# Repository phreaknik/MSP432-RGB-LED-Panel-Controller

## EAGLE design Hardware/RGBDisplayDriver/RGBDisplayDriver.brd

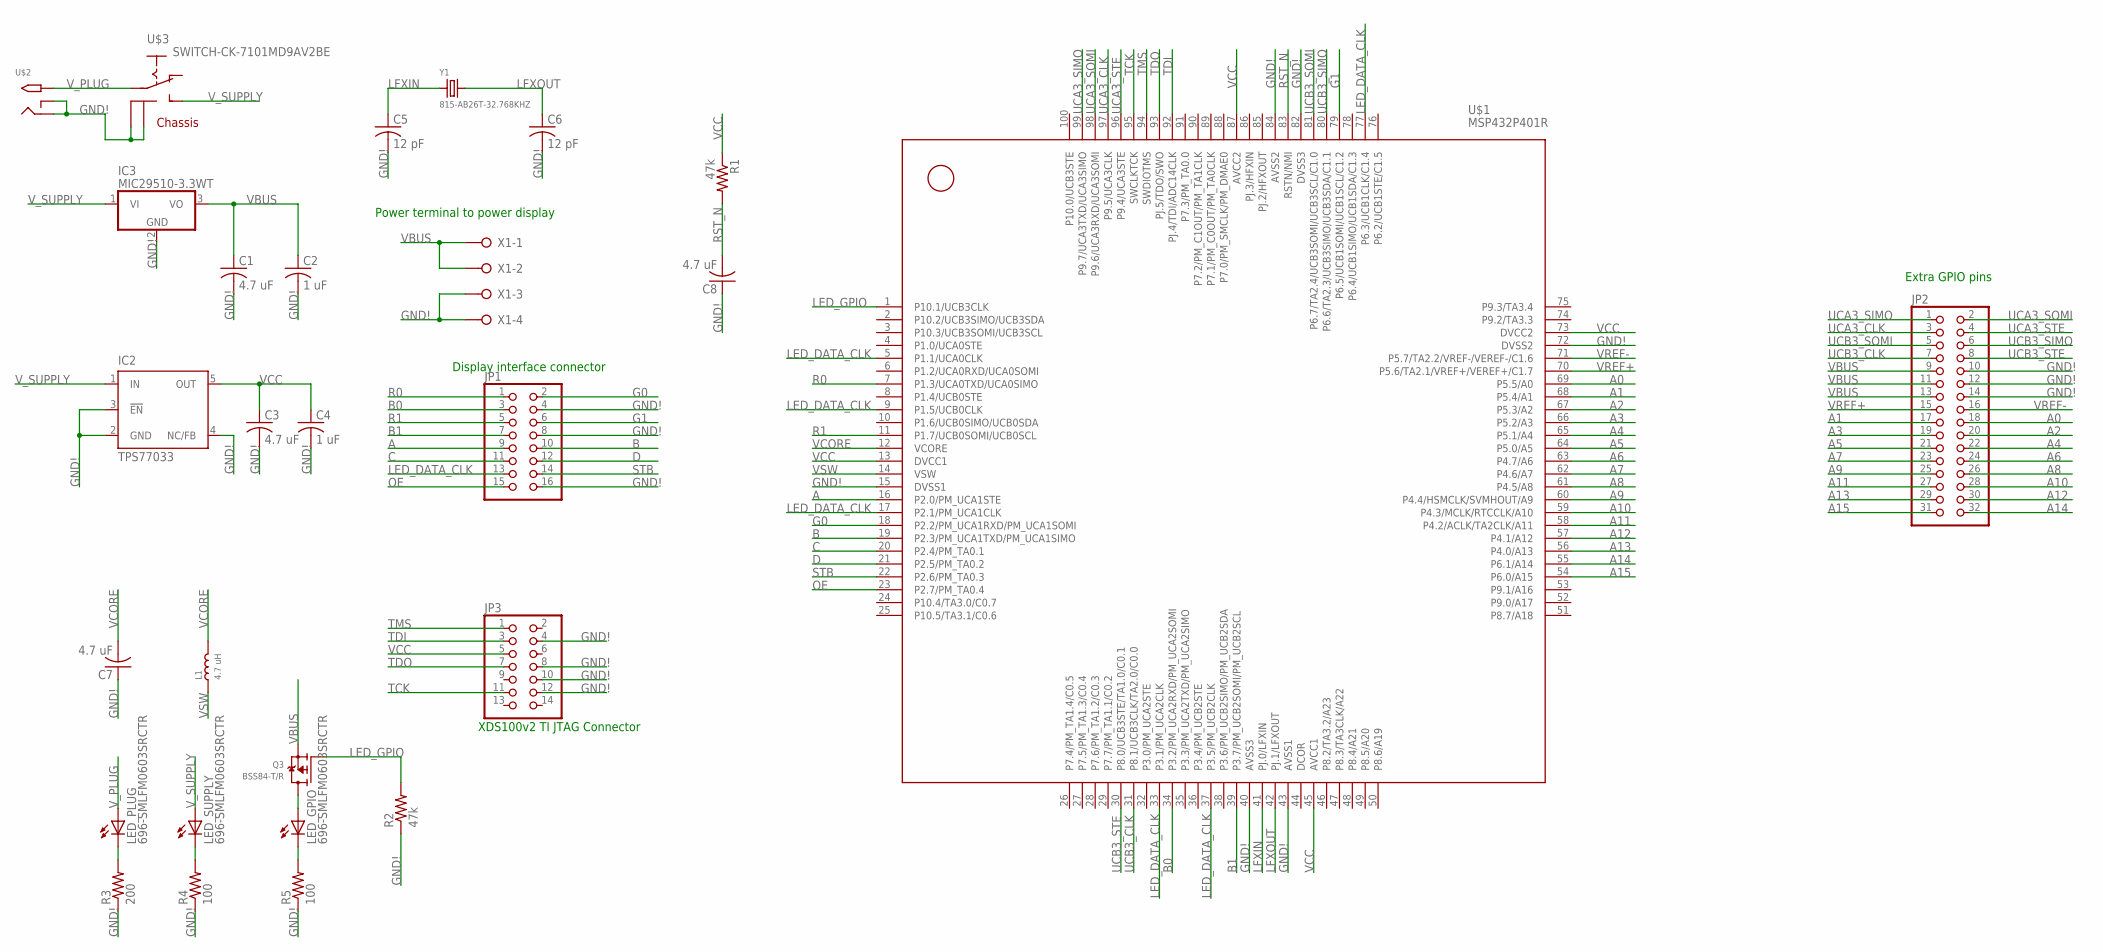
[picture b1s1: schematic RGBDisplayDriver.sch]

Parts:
C1, C3, C7, C8: 4.7 uF; C0603
C2, C4: 1 uF; C0603
C5, C6: 12 pF; C0603
IC2: TPS77033; SOT23-DBV
IC3: MIC29510-3.3WT; TO220V
JP1: PINHD-2X8; 2X08
JP2: PINHD-2X16; 2X16
JP3: PINHD-2X7; 2X07
L1: 4.7 uH; L0603
LED_GPIO: 696-SMLFM0603SRCTR; CHIPLED_0603
LED_PLUG: 696-SMLFM0603SRCTR; CHIPLED_0603
LED_SUPPLY: 696-SMLFM0603SRCTR; CHIPLED_0603
Q3: BSS84-T/R; SOT23-WIDE
R1, R2: 47k; R0603
R3: 200; R0603
R4, R5: 100; R0603
U$1: MSP432P401R; LQFP100
U$2: 2.1MMJACKTHM; PJ-102A
U$3: SWITCH-CK-7101MD9AV2BE
X1: W237-04P; W237-4P
Y1: 815-AB26T-32.768KHZ; CRYSTAL_CYL_2X6MM_SMT

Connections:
A: JP1.9, U$1.16 (P2.0/PM_UCA1STE)
A0: JP2.18, U$1.69 (P5.5/A0)
A1: JP2.17, U$1.68 (P5.4/A1)
A2: JP2.20, U$1.67 (P5.3/A2)
A3: JP2.19, U$1.66 (P5.2/A3)
A4: JP2.22, U$1.65 (P5.1/A4)
A5: JP2.21, U$1.64 (P5.0/A5)
A6: JP2.24, U$1.63 (P4.7/A6)
A7: JP2.23, U$1.62 (P4.6/A7)
A8: JP2.26, U$1.61 (P4.5/A8)
A9: JP2.25, U$1.60 (P4.4/HSMCLK/SVMHOUT/A9)
A10: JP2.28, U$1.59 (P4.3/MCLK/RTCCLK/A10)
A11: JP2.27, U$1.58 (P4.2/ACLK/TA2CLK/A11)
A12: JP2.30, U$1.57 (P4.1/A12)
A13: JP2.29, U$1.56 (P4.0/A13)
A14: JP2.32, U$1.55 (P6.1/A14)
A15: JP2.31, U$1.54 (P6.0/A15)
B: JP1.10, U$1.19 (P2.3/PM_UCA1TXD/PM_UCA1SIMO)
B0: JP1.3, U$1.34 (P3.2/PM_UCA2RXD/PM_UCA2SOMI)
B1: JP1.7, U$1.39 (P3.7/PM_UCB2SOMI/PM_UCB2SCL)
C: JP1.11, U$1.20 (P2.4/PM_TA0.1)
D: JP1.12, U$1.21 (P2.5/PM_TA0.2)
G0: JP1.2, U$1.18 (P2.2/PM_UCA1RXD/PM_UCA1SOMI)
G1: JP1.6, U$1.79 (P6.5/UCB1SOMI/UCB1SCL/C1.2)
GND!: C1.2, C2.2, C3.2, C4.2, C5.2, C6.2, C7.1, C8.1, IC2.2 (GND), IC2.3 (!EN), IC2.4 (NC/FB), IC3.2 (GND), JP1.4, JP1.8, JP1.16, JP2.10, JP2.12, JP2.14, JP3.4, JP3.8, JP3.10, JP3.12, R2.1, R3.1, R4.1, R5.1, U$1.15 (DVSS1), U$1.40 (AVSS3), U$1.43 (AVSS1), U$1.72 (DVSS2), U$1.82 (DVSS3), U$1.84 (AVSS2), U$2.RING, U$2.RING_SW, U$3.P$4, U$3.P$5, X1.3, X1.4
LED_DATA_CLK: JP1.13, U$1.5 (P1.1/UCA0CLK), U$1.9 (P1.5/UCB0CLK), U$1.17 (P2.1/PM_UCA1CLK), U$1.33 (P3.1/PM_UCA2CLK), U$1.37 (P3.5/PM_UCB2CLK), U$1.77 (P6.3/UCB1CLK/C1.4)
LED_GPIO: Q3.1 (G), R2.2, U$1.1 (P10.1/UCB3CLK)
LFXIN: C5.1, U$1.41 (PJ.0/LFXIN), Y1.1
LFXOUT: C6.1, U$1.42 (PJ.1/LFXOUT), Y1.2
unnamed: LED_GPIO.A, Q3.3 (D)
unnamed: LED_PLUG.C, R3.2
unnamed: LED_SUPPLY.C, R4.2
unnamed: LED_GPIO.C, R5.2
OE: JP1.15, U$1.23 (P2.7/PM_TA0.4)
R0: JP1.1, U$1.7 (P1.3/UCA0TXD/UCA0SIMO)
R1: JP1.5, U$1.11 (P1.7/UCB0SOMI/UCB0SCL)
RST_N: C8.2, R1.2, U$1.83 (RSTN/NMI)
STB: JP1.14, U$1.22 (P2.6/PM_TA0.3)
TCK: JP3.11, U$1.95 (SWCLKTCK)
TDI: JP3.3, U$1.92 (PJ.4/TDI/ADC14CLK)
TDO: JP3.7, U$1.93 (PJ.5/TDO/SWO)
TMS: JP3.1, U$1.94 (SWDIOTMS)
UCA3_CLK: JP2.3, U$1.97 (P9.5/UCA3CLK)
UCA3_SIMO: JP2.1, U$1.99 (P9.7/UCA3TXD/UCA3SIMO)
UCA3_SOMI: JP2.2, U$1.98 (P9.6/UCA3RXD/UCA3SOMI)
UCA3_STE: JP2.4, U$1.96 (P9.4/UCA3STE)
UCB3_CLK: JP2.7, U$1.31 (P8.1/UCB3CLK/TA2.0/C0.0)
UCB3_SIMO: JP2.6, U$1.80 (P6.6/TA2.3/UCB3SIMO/UCB3SDA/C1.1)
UCB3_SOMI: JP2.5, U$1.81 (P6.7/TA2.4/UCB3SOMI/UCB3SCL/C1.0)
UCB3_STE: JP2.8, U$1.30 (P8.0/UCB3STE/TA1.0/C0.1)
VBUS: C1.1, C2.1, IC3.3 (VO), JP2.9, JP2.11, JP2.13, Q3.2 (S), X1.1, X1.2
VCC: C3.1, C4.1, IC2.5 (OUT), JP3.5, R1.1, U$1.13 (DVCC1), U$1.45 (AVCC1), U$1.73 (DVCC2), U$1.87 (AVCC2)
VCORE: C7.2, L1.2, U$1.12 (VCORE)
VREF+: JP2.15, U$1.70 (P5.6/TA2.1/VREF+/VEREF+/C1.7)
VREF-: JP2.16, U$1.71 (P5.7/TA2.2/VREF-/VEREF-/C1.6)
VSW: L1.1, U$1.14 (VSW)
V_PLUG: LED_PLUG.A, U$2.TIP, U$3.P$2
V_SUPPLY: IC2.1 (IN), IC3.1 (VI), LED_SUPPLY.A, U$3.P$1

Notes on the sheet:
Power terminal to power display
Display interface connector
Extra GPIO pins
XDS100v2 TI JTAG Connector

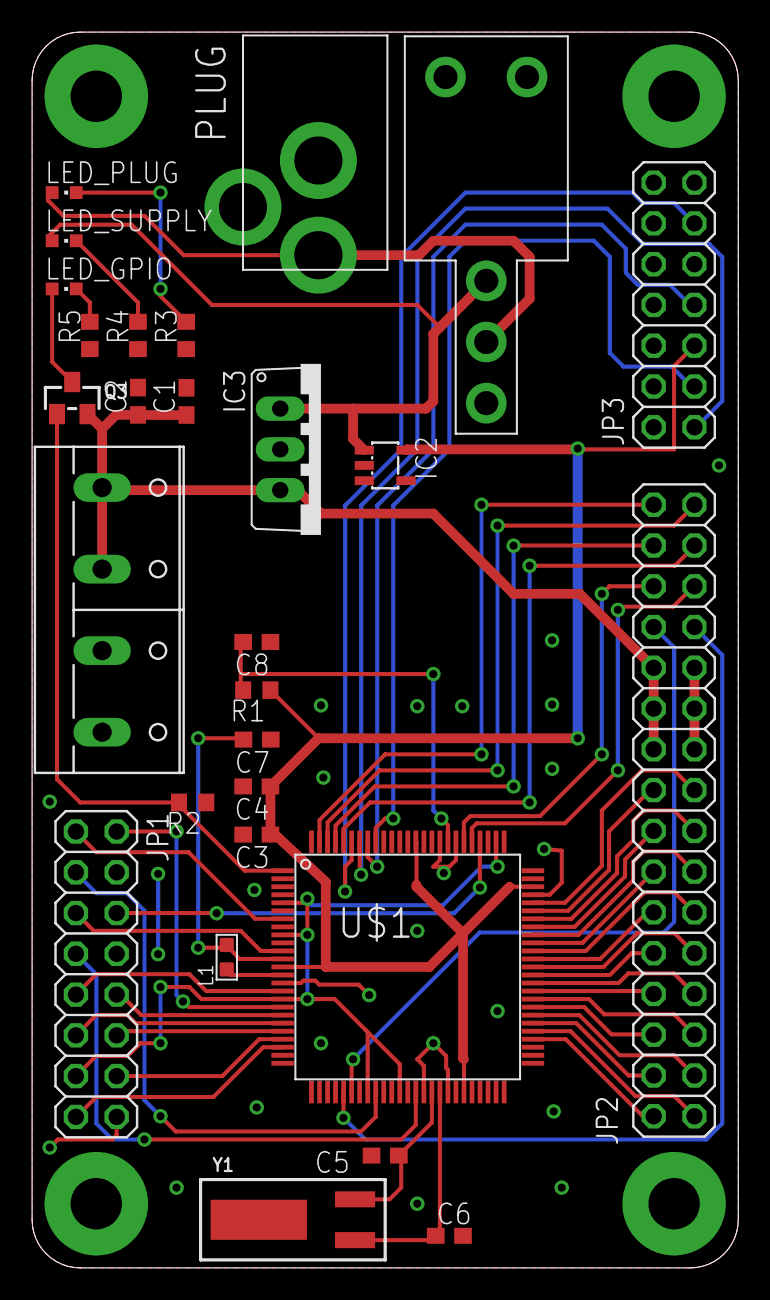
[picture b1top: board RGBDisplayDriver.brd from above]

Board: 2 copper layers, 44.0 x 77.0 mm, 28 parts (0 on the bottom side), 58 nets.

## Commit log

2015-12-02 :circus_tent: Added .gitattributes & .gitignore files
2015-12-02 Ignored .launches
2015-12-03 Ignored Debug/ folder and .prefs files
2015-12-03 testing
2015-12-03 Reverted to remove bad 'OLD' statement
2015-12-03 Restructured Repository to include firmware and hardware directories
2015-12-03 Fixing bad commit status
2015-12-03 Fixing up CCS workspace
2015-12-03 Added test firmwares
    -DisplayDriver-Test-BlinkLED: Blinks the LED to verify the PCB
    -DisplayDriver-Test-HardCodedText: Displays hardcoded text to test the
    display
2015-12-03 Still fixing CCS workspace
2015-12-03 Added hardware design files
2015-12-03 Ignored .metadata files
2015-12-03 Completed drawRect()
2015-12-03 Fixed ignore for .metadata
2015-12-03 Ignored metadata
2015-12-03 Updated metadata files
2015-12-03 Added PDF schematic
2015-12-03 Renamed Hardware\RGBDisplayDriver to Hardware\EagleCAD
2015-12-03 Removing metadata files from repo
2015-12-03 removing metadata files
2015-12-04 Fixed bug and cleaned up code
    - Added limits to the color values in setColorPDM()
    - Removed #define DISP__COLOR_BITS because it is unused
2015-12-04 Added RemoteSystemsTempFiles to ignore list
2015-12-04 removed from repo
2015-12-04 Ignored .metadata/
2015-12-04 Moving library to its own repository
2015-12-04 Adding RGB-LED-Panel-Library as submodule
2015-12-04 Revert "Moving library to its own repository"
    This reverts commit f2be998cd43827d8f55b344d57a48adc7ecefbc0.
2015-12-04 Temp
2015-12-04 Revert "Adding RGB-LED-Panel-Library as submodule"
    This reverts commit b664f91dc61b45637774f31538c26f3a898435c4.
2015-12-04 Fixed #include directories
2015-12-04 Ignored RemoteSystemsTempFiles/
2015-12-04 Fixed include directories
2015-12-04 Completed drawChar()
2015-12-04 [ WIP ] Added charMap, but not complete
2015-12-04 charMap completed
2015-12-04 char_map.h completed - all characters have been added
2015-12-04 Fixed bug with drawRect() drawing off-screen (GitHub issue #6)
2015-12-04 Cleaned up font style
2015-12-04 Displays test graphic for rectangles and characters
2015-12-07 Added
2015-12-23 Added include option for driverLib
2015-12-23 Added drawCircle() example to main
2015-12-23 Updated drawCircle() function parameters
2015-12-23 [WIP] Updated drawCircle()
2015-12-23 [WIP] Modified drawCircle() to draw a filled in circle, not just outline.
2016-01-02 Changed circle radius
2016-01-02 Improved drawCircle()
2016-01-02 Complete overhaul of drawCircle() to make it much more efficient
2016-01-02 completed drawCircle()
2016-01-02 Modified drawCircle() test code
2016-01-02 Created drawLine(), but still can't draw 'steep' lines
2016-01-02 added drawPixel
2016-01-02 Fixed drawLine() so that it can draw steep lines
2016-01-02 Added vertical line to test image
2016-01-02 added drawPixel()
2016-01-02 Added fillXXX functions
2016-01-02 removed unnecessary fillPixel() and fillLine()
2016-01-02 removed hardcoded screen size parameters from all drawXXX functions, so that they can be used for arbitrary screen sizes
2016-01-02 removed for() loop from drawRect() to make it more CPU efficient
2016-01-02 Fixed drawRect() to only draw outline
2016-01-02 Fixed drawCircle() to only draw outline
2016-01-02 Fixed drawChar() warnings
2016-01-03 fixed drawChar() so that it can handle strings
2016-01-03 Test animation hard coded. Needs process manager to arbitrate between animation and display driver

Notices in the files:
parts and their libraries:
microbuilder: This work is placed in the public domain, and may be freely used for commercial and non-commercial work with the following conditions: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
